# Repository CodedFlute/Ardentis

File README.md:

# Ardentis

> **⚠ WARNING:** This is currently a work in progress and untested. Only fly if you are willing and able to take full responsibility for any damage or property loss that may result from failure of this flight computer to operate as designed.

Ardentis is the best value high-performance flight computer designed specifically for high-power rocketry at all levels from 38mm min diameter to 132mm dual stage space shots.

This repository contains both the hardware and software required for Ardentis and its upgrades.

## Features

Ardentis comes in one default configurations, although any combination of features could be created by due to its open source design philosophy.

| Feature | Capability |
|-|-|
| Max Altitude | Baro: 25 km (85k ft) GPS: 80 km (250k ft) |
| GPS Tracking | Yes |
| Max Radio Range | ~15 km |
| Max Acceleration | 400G |
| Outputs | 4 (Servo + Air Start Capable) |
| Data Logging | MicroSD |
| Wi-Fi | Configuration and Control |

### Ardentis

<details>
<summary>Hardware Details</summary>

- **MCU**: ESP32-S3-MINI-1-N4R2
  - 4 MB Flash
  - 384 KB ROM
  - 512 KB SRAM
  - Dual core Xtense 32 bit LX7 at up to 240 MHz
- **Radio**: seeed studio SX126x Breakout
  - 22 dBm TX Power
  - 915 MHz ISM Band
  - u.Fl Antenna Connector
- **IMU**: ICM
  - +/- 16G Accelerometer
  - +/- 2000 Deg/s Gyroscope
- **High G Accelerometer**:
  - 3 Axis
  - +/- 100, 200, 400G Ranges
- **Barometer**: MS5611
  - 10 cm Resolution
  - 10 mBar to 1 200 mBar Operating Range
- **GPS**: uBlox SAM-M10Q
  - 80 km (250k ft) Max Altitude
  - 500 m/s (1.45 Mach) Max Velocity
  - 4G Max Acceleration
- **Ignition Channels**4
- **Connectivity**: Bluetooth 5.0, Wi-Fi, Micro USB
- **Power**: 1S LiPo battery support (or anything between 2V and 5V)

</details>

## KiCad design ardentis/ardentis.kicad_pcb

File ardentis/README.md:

# Hardware

This folder contains the KiCAD files for the Ardentis hardware. These were made using KiCAD 9.0.

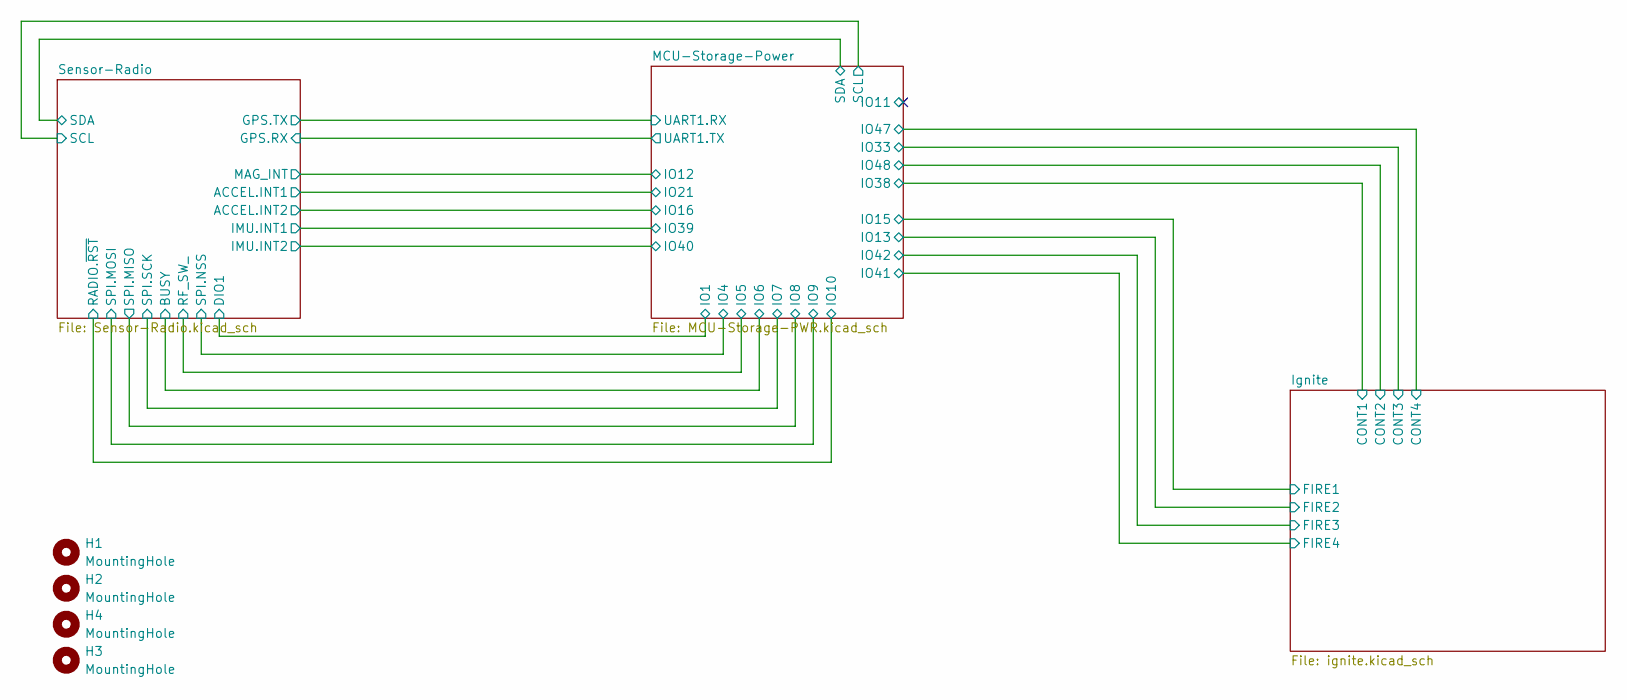
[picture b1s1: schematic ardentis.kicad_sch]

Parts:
H1, H2, H3, H4: MountingHole; MountingHole_3.5mm_Pad

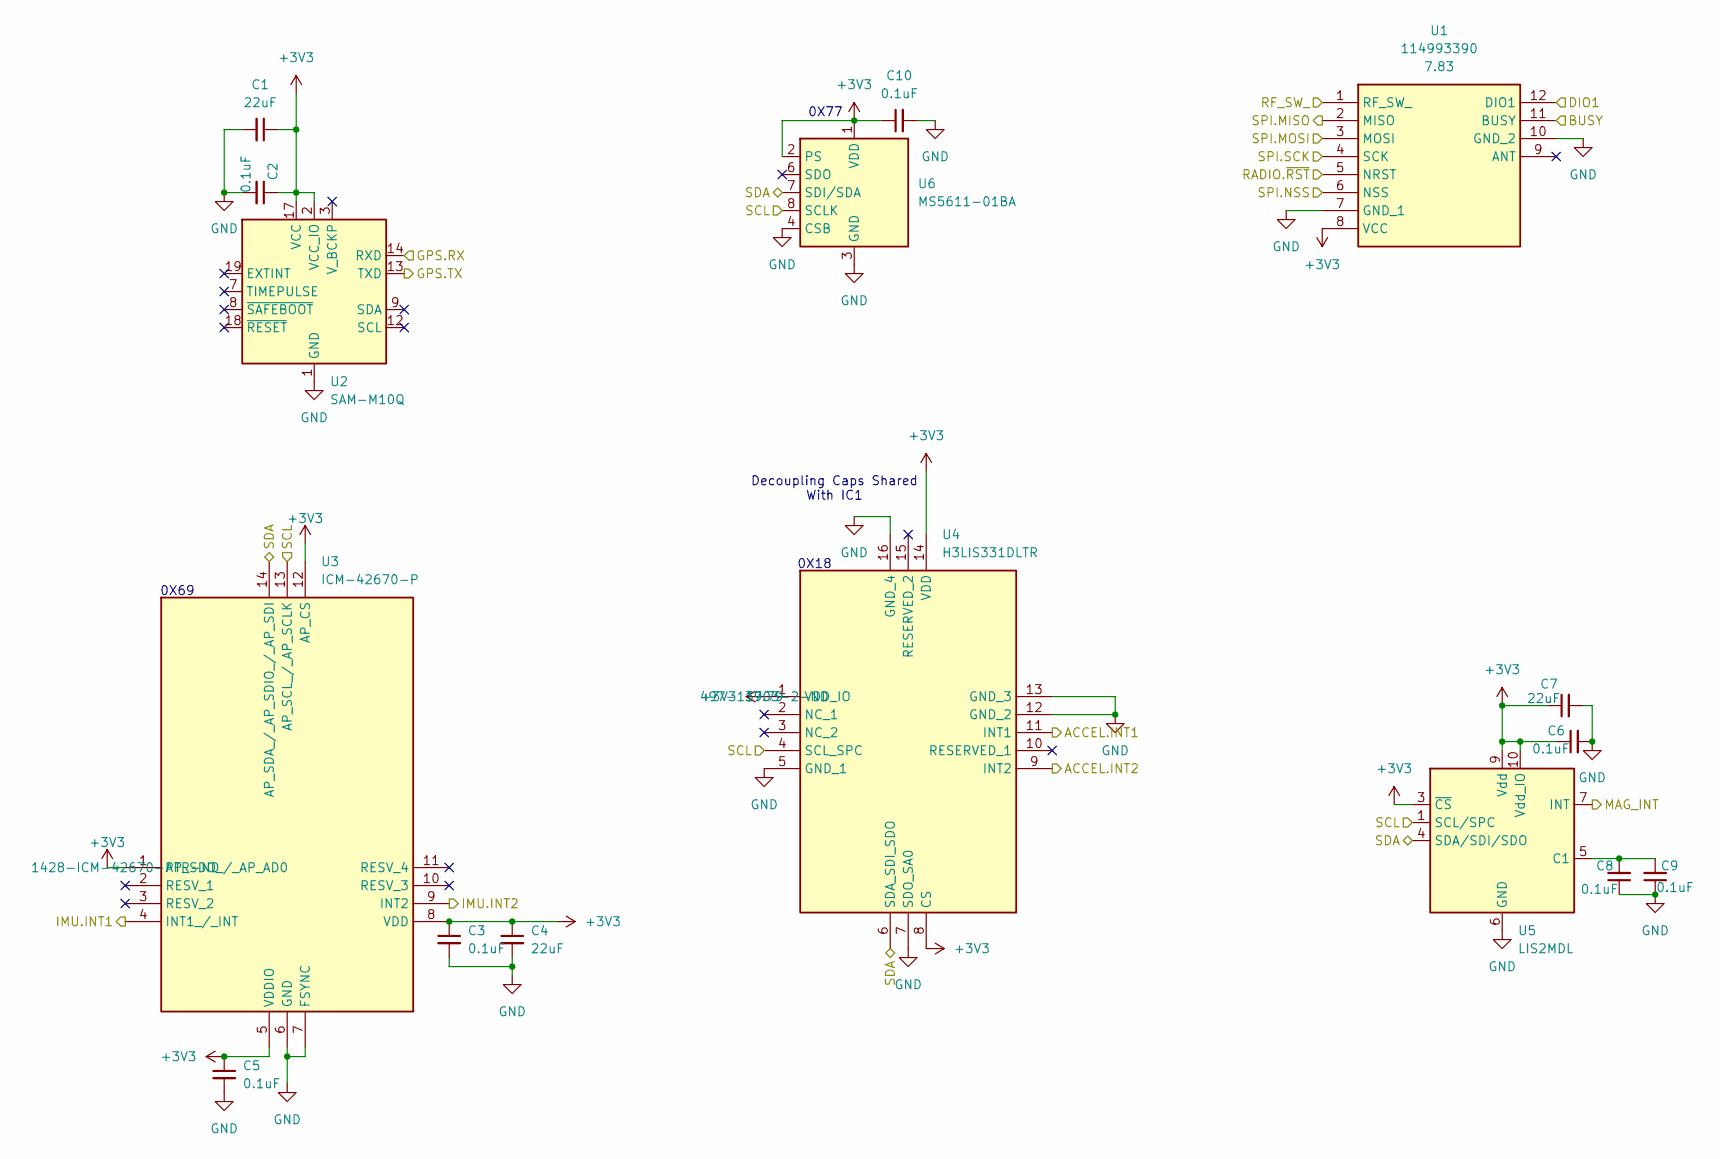
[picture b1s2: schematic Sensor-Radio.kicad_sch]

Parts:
C1, C4, C7: 22uF; C_0805_2012Metric_Pad1.18x1.45mm_HandSolder; Manufacturer_Part_Number CL21X226MQQNNNE; Mouser Part Number 81-GRM21BZ70J226ME4L
C2, C3, C5, C6, C8, C9, C10: 0.1uF; C_0805_2012Metric_Pad1.18x1.45mm_HandSolder; Manufacturer_Part_Number KGM21NR71H104KT; Mouser Part Number 581-08053C104K
U1: 114993390; Mouser Part Number 713-114993390
U2: SAM-M10Q; ublox_SAM-M10Q
U3: ICM-42670-P; ICM42670P; Mouser Part Number 410-ICM-42670-P
U4: H3LIS331DLTR; Mouser Part Number 511-H3LIS331DLTR
U5: LIS2MDL; LGA-12_2x2mm_P0.5mm; Manufacturer_Part_Number LIS2MDLTR
U6: MS5611-01BA; LGA-8_3x5mm_P1.25mm; Manufacturer_Part_Number MS561101BA03-50

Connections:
+3V3: C1.1, C2.1, C3.1, C4.1, C5.1, C6.1, C7.1, C10.1, U1.8 (VCC), U2.2 (VCC_IO), U2.17 (VCC), U3.1 (AP_SDO_/_AP_AD0), U3.5 (VDDIO), U3.8 (VDD), U3.12 (AP_CS), U4.1 (VDD_IO), U4.8 (CS), U4.14 (VDD), U5.3 (~CS), U5.9 (Vdd), U5.10 (Vdd_IO), U6.1 (VDD), U6.2 (PS); also elsewhere on the board
/MCU-Storage-Power/IO1: U1.12 (DIO1); also elsewhere on the board
/MCU-Storage-Power/IO4: U1.6 (NSS); also elsewhere on the board
/MCU-Storage-Power/IO5: U1.1 (RF_SW_); also elsewhere on the board
/MCU-Storage-Power/IO6: U1.11 (BUSY); also elsewhere on the board
/MCU-Storage-Power/IO7: U1.4 (SCK); also elsewhere on the board
/MCU-Storage-Power/IO8: U1.2 (MISO); also elsewhere on the board
/MCU-Storage-Power/IO9: U1.3 (MOSI); also elsewhere on the board
/MCU-Storage-Power/IO10: U1.5 (NRST); also elsewhere on the board
/MCU-Storage-Power/IO12: U5.7 (INT); also elsewhere on the board
/MCU-Storage-Power/IO16: U4.9 (INT2); also elsewhere on the board
/MCU-Storage-Power/IO21: U4.11 (INT1); also elsewhere on the board
/MCU-Storage-Power/IO39: U3.4 (INT1_/_INT); also elsewhere on the board
/MCU-Storage-Power/IO40: U3.9 (INT2); also elsewhere on the board
/MCU-Storage-Power/SCL: U3.13 (AP_SCL_/_AP_SCLK), U4.4 (SCL_SPC), U5.1 (SCL/SPC), U6.8 (SCLK); also elsewhere on the board
/MCU-Storage-Power/SDA: U3.14 (AP_SDA_/_AP_SDIO_/_AP_SDI), U4.6 (SDA_SDI_SDO), U5.4 (SDA/SDI/SDO), U6.7 (SDI/SDA); also elsewhere on the board
/MCU-Storage-Power/UART1.RX: U2.13 (TXD); also elsewhere on the board
/MCU-Storage-Power/UART1.TX: U2.14 (RXD); also elsewhere on the board
GND: C1.2, C2.2, C3.2, C4.2, C5.2, C6.2, C7.2, C8.1, C9.1, C10.2, U1.7 (GND_1), U1.10 (GND_2), U2.1 (GND), U2.4 (GND), U2.5 (GND), U2.6 (GND), U2.10 (GND), U2.11 (GND), U2.15 (GND), U2.16 (GND), U2.20 (GND), U3.6 (GND), U3.7 (FSYNC), U4.5 (GND_1), U4.7 (SDO_SA0), U4.12 (GND_2), U4.13 (GND_3), U4.16 (GND_4), U5.6 (GND), U5.8 (GND), U6.3 (GND), U6.4 (CSB), U6.5 (CSB); also elsewhere on the board
unnamed: C8.2, C9.2, U5.5 (C1)

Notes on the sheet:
0X69
0X18
0X77
Decoupling Caps Shared With IC1

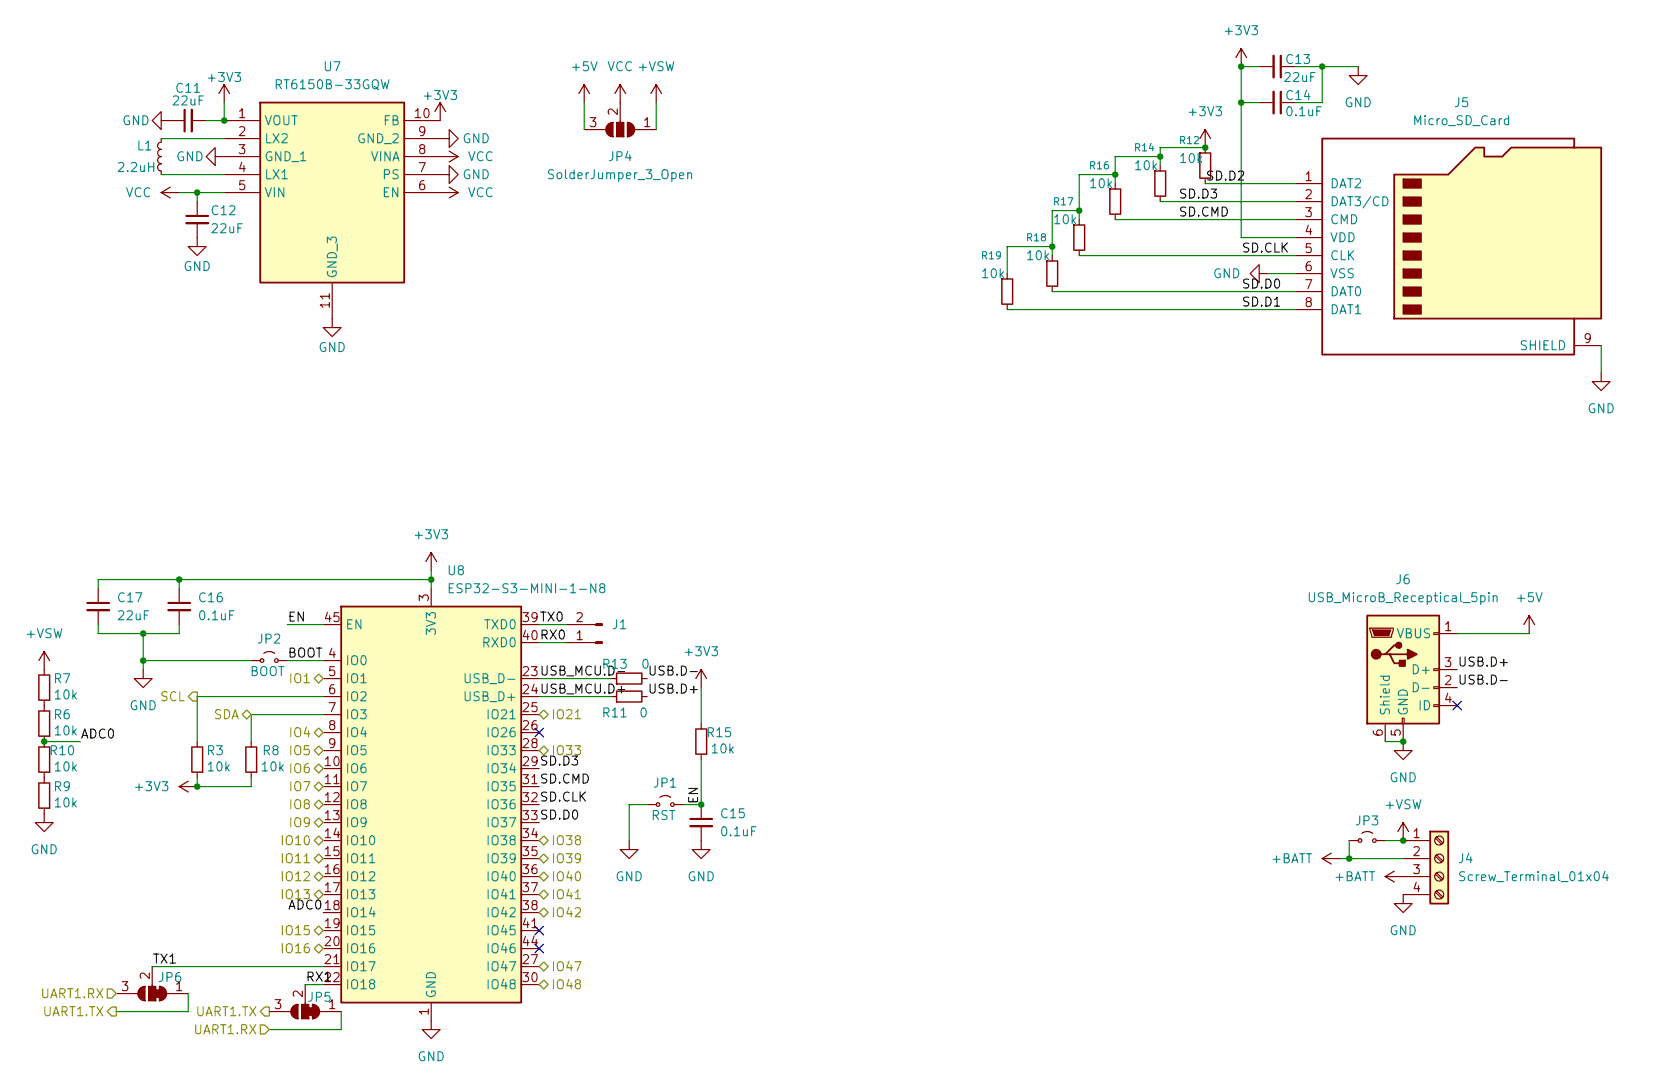
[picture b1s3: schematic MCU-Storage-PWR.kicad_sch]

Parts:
C11, C12, C13, C17: 22uF; C_0805_2012Metric_Pad1.18x1.45mm_HandSolder; Manufacturer_Part_Number CL21X226MQQNNNE; Mouser Part Number 81-GRM21BZ70J226ME4L
C14, C15, C16: 0.1uF; C_0805_2012Metric_Pad1.18x1.45mm_HandSolder; Manufacturer_Part_Number KGM21NR71H104KT; Mouser Part Number 581-08053C104K
J1: Conn_01x02_Pin; TestPoint_2Pads_Pitch2.54mm_Drill0.8mm
J4: Screw_Terminal_01x04; TB00150004BE; Manufacturer_Part_Number TB001-500-04BE
J5: Micro_SD_Card; MEM20670218000A; Manufacturer_Part_Number MEM2067-02-180-00-A; Mouser Part Number 640-MEM20670218000A
J6: USB_MicroB_Receptical_5pin; UJ2MIBHGSMTTR; Manufacturer_Part_Number UJ2-MIBH-G-SMT-TR; Mouser Part Number 490-UJ2-MIBH-G-SMTTR
JP1: RST; TestPoint_2Pads_Pitch2.54mm_Drill0.8mm
JP2: BOOT; TestPoint_2Pads_Pitch2.54mm_Drill0.8mm
JP3: Jumper_2_Small_Open; SolderJumper-2_P1.3mm_Open_TrianglePad1.0x1.5mm
JP4: SolderJumper_3_Open; SolderJumper-3_P2.0mm_Open_TrianglePad1.0x1.5mm
JP5, JP6: SolderJumper_3_Bridged12; SolderJumper-3_P2.0mm_Open_TrianglePad1.0x1.5mm
L1: 2.2uH; L_1008_2520Metric_Pad1.43x2.20mm_HandSolder; Manufacturer_Part_Number WIP252012S-2R2MLDG; Mouser Part Number 652-SRN2510F-2R2M
R3, R6, R7, R8, R9, R10, R12, R14, R15, R16, R17, R18, R19: 10k; R_0805_2012Metric_Pad1.20x1.40mm_HandSolder; Manufacturer_Part_Number RC0805JR-0710KL; Mouser Part Number 660-RK73B2ATTD103J
R11, R13: 0; R_0805_2012Metric_Pad1.20x1.40mm_HandSolder; Manufacturer_Part_Number ERJ-6GEY0R00V; Mouser Part Number 660-RK73Z2ATTD
U7: RT6150B-33GQW; SON50P250X250X80-11N-D; Mouser Part Number 835-RT6150B-33GQW
U8: ESP32-S3-MINI-1-N8; ESP32-S3-MINI-1; Manufacturer_Part_Number 1965-ESP32-S3-MINI-1-N4R2TR-ND; Mouser Part Number 356-ESP32-MINI1PH3Q0

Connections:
+3V3: C11.2, C13.2, C14.2, C16.1, C17.1, J5.4 (VDD), R3.1, R8.1, R12.1, R14.1, R15.2, R16.1, R17.1, R18.1, R19.1, U7.1 (VOUT), U7.10 (FB), U8.3 (3V3); also elsewhere on the board
+5V: J6.1 (VBUS), JP4.3 (B)
+BATT: J4.2, J4.3, JP3.1 (A)
+VSW: J4.1, JP3.2 (B), JP4.1 (A), R7.2; also elsewhere on the board
/Ignite/CONT1: U8.34 (IO38); also elsewhere on the board
/Ignite/CONT2: U8.30 (IO48); also elsewhere on the board
/Ignite/CONT3: U8.28 (IO33); also elsewhere on the board
/Ignite/CONT4: U8.27 (IO47); also elsewhere on the board
/Ignite/FIRE1: U8.19 (IO15); also elsewhere on the board
/Ignite/FIRE2: U8.17 (IO13); also elsewhere on the board
/Ignite/FIRE3: U8.38 (IO42); also elsewhere on the board
/Ignite/FIRE4: U8.37 (IO41); also elsewhere on the board
/MCU-Storage-Power/ADC0: R6.1, R10.2, U8.18 (IO14)
/MCU-Storage-Power/BOOT: JP2.2 (B), U8.4 (IO0)
/MCU-Storage-Power/EN: C15.1, JP1.2 (B), R15.1, U8.45 (EN)
/MCU-Storage-Power/IO1: U8.5 (IO1); also elsewhere on the board
/MCU-Storage-Power/IO4: U8.8 (IO4); also elsewhere on the board
/MCU-Storage-Power/IO5: U8.9 (IO5); also elsewhere on the board
/MCU-Storage-Power/IO6: U8.10 (IO6); also elsewhere on the board
/MCU-Storage-Power/IO7: U8.11 (IO7); also elsewhere on the board
/MCU-Storage-Power/IO8: U8.12 (IO8); also elsewhere on the board
/MCU-Storage-Power/IO9: U8.13 (IO9); also elsewhere on the board
/MCU-Storage-Power/IO10: U8.14 (IO10); also elsewhere on the board
/MCU-Storage-Power/IO11: U8.15 (IO11)
/MCU-Storage-Power/IO12: U8.16 (IO12); also elsewhere on the board
/MCU-Storage-Power/IO16: U8.20 (IO16); also elsewhere on the board
/MCU-Storage-Power/IO21: U8.25 (IO21); also elsewhere on the board
/MCU-Storage-Power/IO39: U8.35 (IO39); also elsewhere on the board
/MCU-Storage-Power/IO40: U8.36 (IO40); also elsewhere on the board
/MCU-Storage-Power/RX0: J1.1, U8.40 (RXD0)
/MCU-Storage-Power/RX1: JP5.2 (C), U8.22 (IO18)
/MCU-Storage-Power/SCL: R3.2, U8.6 (IO2); also elsewhere on the board
/MCU-Storage-Power/SD.CLK: J5.5 (CLK), R17.2, U8.32 (IO36)
/MCU-Storage-Power/SD.CMD: J5.3 (CMD), R16.2, U8.31 (IO35)
/MCU-Storage-Power/SD.D0: J5.7 (DAT0), R18.2, U8.33 (IO37)
/MCU-Storage-Power/SD.D1: J5.8 (DAT1), R19.2
/MCU-Storage-Power/SD.D2: J5.1 (DAT2), R12.2
/MCU-Storage-Power/SD.D3: J5.2 (DAT3/CD), R14.2, U8.29 (IO34)
/MCU-Storage-Power/SDA: R8.2, U8.7 (IO3); also elsewhere on the board
/MCU-Storage-Power/TX0: J1.2, U8.39 (TXD0)
/MCU-Storage-Power/TX1: JP6.2 (C), U8.21 (IO17)
/MCU-Storage-Power/UART1.RX: JP5.1 (A), JP6.3 (B); also elsewhere on the board
/MCU-Storage-Power/UART1.TX: JP5.3 (B), JP6.1 (A); also elsewhere on the board
/MCU-Storage-Power/USB.D+: J6.3 (D+), R11.2
/MCU-Storage-Power/USB.D-: J6.2 (D-), R13.2
/MCU-Storage-Power/USB_MCU.D+: R11.1, U8.24 (USB_D+)
/MCU-Storage-Power/USB_MCU.D-: R13.1, U8.23 (USB_D-)
GND: C11.1, C12.2, C13.1, C14.1, C15.2, C16.2, C17.2, J4.4, J5.6 (VSS), J5.9 (SHIELD), J6.5 (GND), J6.6 (Shield), JP1.1 (A), JP2.1 (A), R9.1, U7.3 (GND_1), U7.7 (PS), U7.9 (GND_2), U7.11 (GND_3), U8.1 (GND), U8.2 (GND), U8.42 (GND), U8.43 (GND), U8.46 (GND), U8.47 (GND), U8.48 (GND), U8.49 (GND), U8.50 (GND), U8.51 (GND), U8.52 (GND), U8.53 (GND), U8.54 (GND), U8.55 (GND), U8.56 (GND), U8.57 (GND), U8.58 (GND), U8.59 (GND), U8.60 (GND), U8.61 (GND), U8.62 (GND), U8.63 (GND), U8.64 (GND), U8.65 (GND); also elsewhere on the board
unnamed: R6.2, R7.1
unnamed: R9.2, R10.1
unnamed: L1.1, U7.4 (LX1)
unnamed: L1.2, U7.2 (LX2)
VCC: C12.1, JP4.2 (C), U7.5 (VIN), U7.6 (EN), U7.8 (VINA)

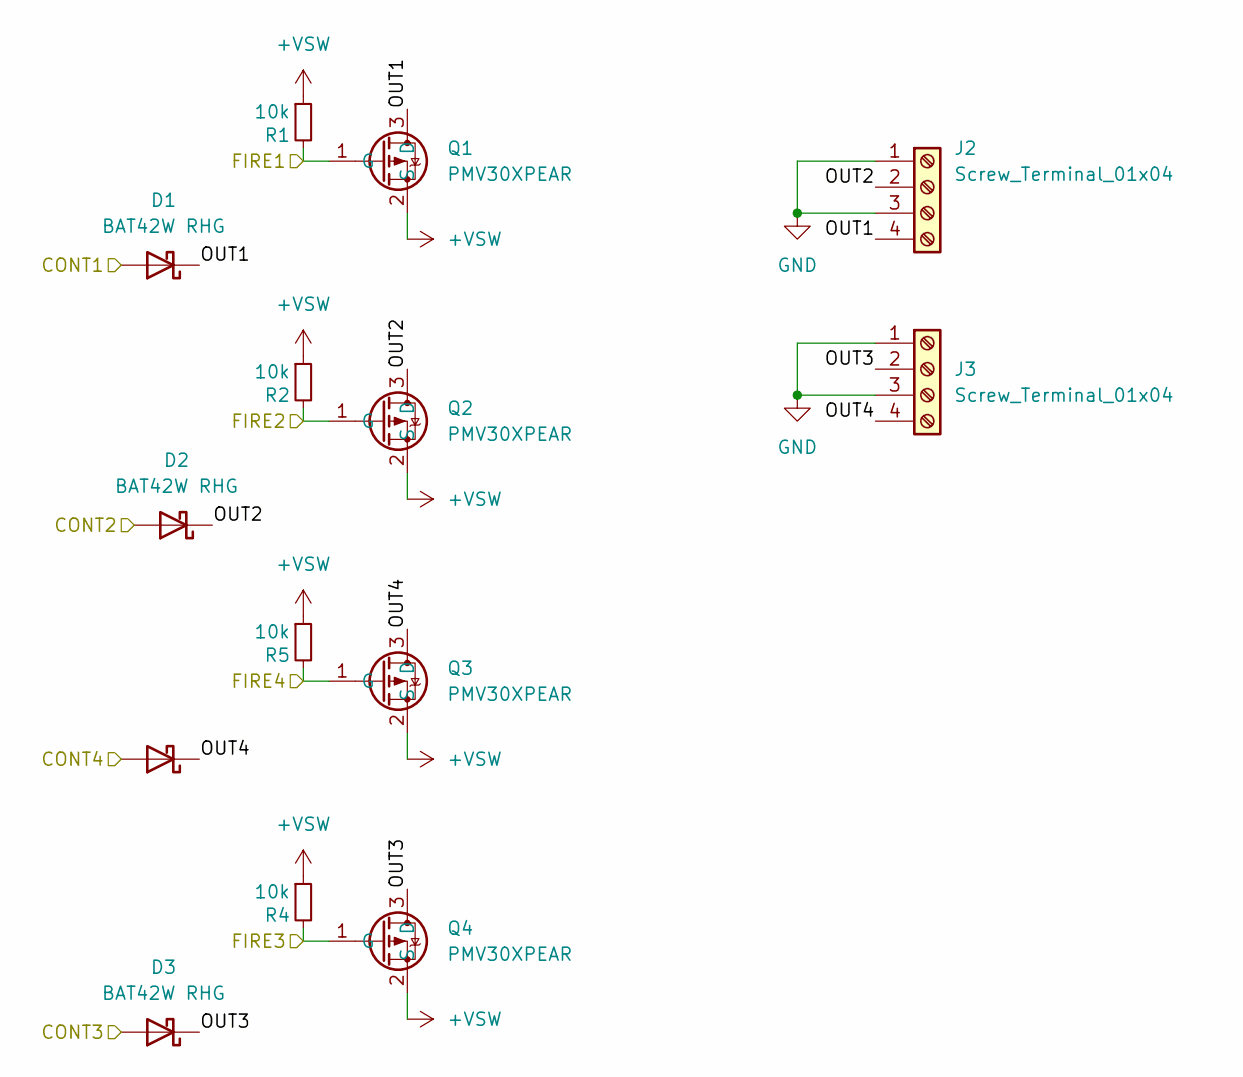
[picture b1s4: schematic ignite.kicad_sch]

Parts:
D1, D2, D3, D4: BAT42W RHG; D_SOD-123; Manufacturer_Part_Number BAT42W RHG
J2, J3: Screw_Terminal_01x04; TB00150004BE; Manufacturer_Part_Number TB001-500-04BE
Q1, Q2, Q3, Q4: PMV30XPEAR; SOT95P230X110-3N; Mouser Part Number 771-PMV30XPEAR
R1, R2, R4, R5: 10k; R_0805_2012Metric_Pad1.20x1.40mm_HandSolder; Manufacturer_Part_Number RC0805JR-0710KL; Mouser Part Number 660-RK73B2ATTD103J

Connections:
+VSW: Q1.2 (S), Q2.2 (S), Q3.2 (S), Q4.2 (S), R1.1, R2.1, R4.1, R5.1; also elsewhere on the board
/Ignite/CONT1: D1.2 (A); also elsewhere on the board
/Ignite/CONT2: D2.2 (A); also elsewhere on the board
/Ignite/CONT3: D3.2 (A); also elsewhere on the board
/Ignite/CONT4: D4.2 (A); also elsewhere on the board
/Ignite/FIRE1: Q1.1 (G), R1.2; also elsewhere on the board
/Ignite/FIRE2: Q2.1 (G), R2.2; also elsewhere on the board
/Ignite/FIRE3: Q4.1 (G), R4.2; also elsewhere on the board
/Ignite/FIRE4: Q3.1 (G), R5.2; also elsewhere on the board
/Ignite/OUT1: D1.1 (K), J2.4, Q1.3 (D)
/Ignite/OUT2: D2.1 (K), J2.2, Q2.3 (D)
/Ignite/OUT3: D3.1 (K), J3.2, Q4.3 (D)
/Ignite/OUT4: D4.1 (K), J3.4, Q3.3 (D)
GND: J2.1, J2.3, J3.1, J3.3; also elsewhere on the board

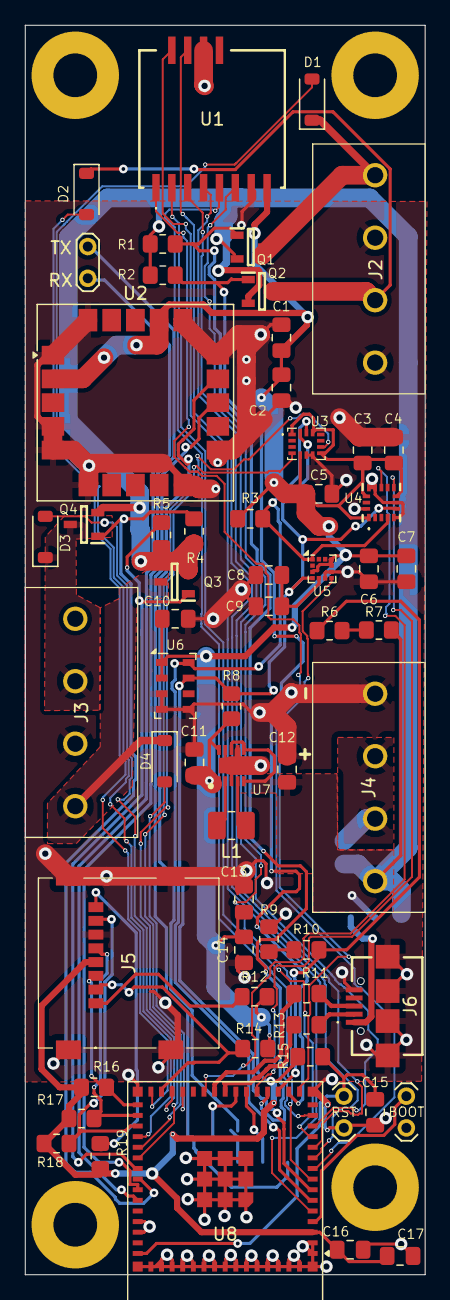
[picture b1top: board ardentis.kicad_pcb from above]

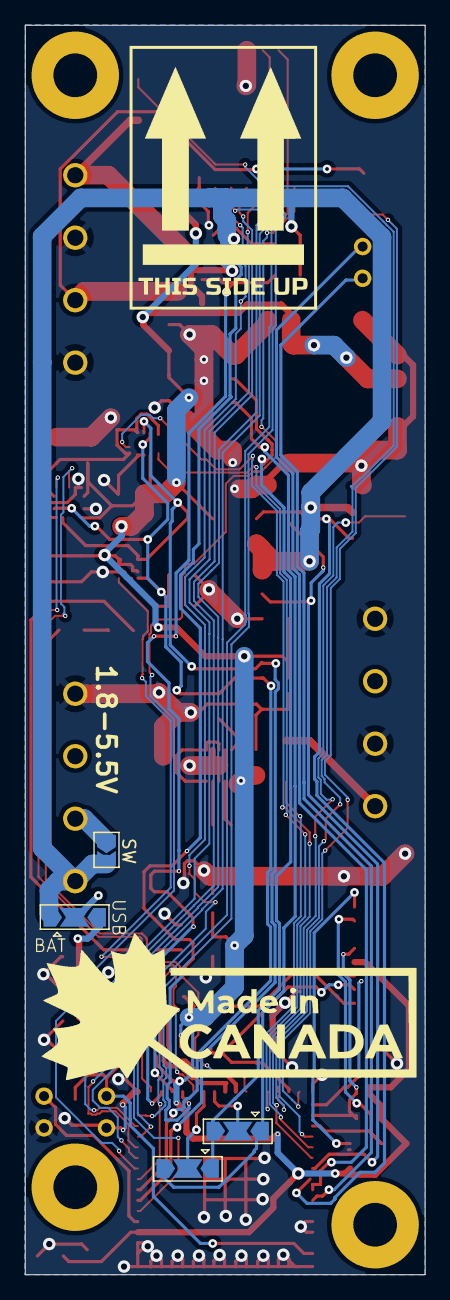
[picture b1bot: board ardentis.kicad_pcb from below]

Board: 2 copper layers, 32.0 x 100.0 mm, 69 parts (4 on the bottom side), 57 nets.

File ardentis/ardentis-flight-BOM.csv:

"Reference","Value","Qty","Manufacturer_Name","Manufacturer_Part_Number","SPN","Price"
"J6","USB_MicroB_Receptical_5pin","1","Same Sky","UJ2-MIBH-G-SMT-TR","2223-UJ2-MIBH-G-SMT-TR-ND","0.67"
"L1","2.2uH","1","INPAQ Technology Co., Ltd","WIP252012S-2R2MLDG","3526-WIP252012S-2R2MLDGTR-ND","0.15"
"R11,R13","0","2","Panasonic Electronic Components","ERJ-6GEY0R00V","P0.0ATR-ND","0.16"
"U1","114993390","1","Seeed Technology Co., Ltd","114993390","1597-114993390-ND","7.83"
"U7","RT6150B-33GQW","1","RICHTEK","RT6150B-33GQW","RT6150B-33GQWTR-ND","4.62"
"U8","ESP32-S3-MINI-1-N4R2","1","Espressif Systems","1965-ESP32-S3-MINI-1-N4R2TR-ND","","8.4"
"C1,C4,C7,C11,C12,C13,C17","22uF","7","Samsung Electro-Mechanics","CL21X226MQQNNNE","1276-3031-2-ND","0.2"
"C2,C3,C5,C6,C8,C9,C10,C14,C15,C16","0.1uF","10","Kyocera AVX","KGM21NR71H104KT","478-KGM21NR71H104KTTR-ND","0.12"
"J2,J3,J4","Screw_Terminal_01x04","3","Same Sky","TB001-500-04BE","102-6136-ND","0.85"
"R1,R2,R3,R4,R5,R6,R7,R8,R9,R10,R12,R14,R15,R16,R17,R18,R19","10k","17","YAGEO","RC0805JR-0710KL","311-10KARTR-ND","0.019"
"D1,D2,D3,D4","BAT42W RHG","4","Taiwan Semiconductor Corporation","BAT42W RHG","BAT42WRHGTR-ND","0.17"
"J5","Micro_SD_Card","1","GCT","MEM2067-02-180-00-A","2073-MEM2067-02-180-00-ATR-ND","1.60"
"Q1,Q2","Q_Dual_PMOS_S1G1D2S2G2D1","2","Goford Semiconductor","G170P02D32","3141-G170P02D32TR-ND","1.01"
"U2","SAM-M10Q","1","","","",""
"U3","ICM-42670-P","1","TDK","ICM-42670-P","1428-ICM-42670-PTR-ND","5.90"
"U4","H3LIS331DLTR","1","STMicroelectronics","H3LIS331DLTR","497-13903-2-ND","17.79"
"U5","LIS2MDL","1","STMicroelectronics","LIS2MDLTR","497-17588-2-ND","3.71"
"U6","MS5611-01BA","1","TE Connectivity Measurement Specialties","MS561101BA03-50","223-1622-2-ND","14.99"

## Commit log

2025-04-09 Initial Design
    Initial Schematic Design
2025-06-08 Initial code
    Initial code. Theoretically will work but not tested due to lack of hardware and updates to PCB.
